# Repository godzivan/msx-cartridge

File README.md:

# MSX Cartridge

Some hardware specs (schematics + PCB designs) to build cartridges for 
MSX system.

## RPMC 
### RPMC is a MSX clone with a real MSX cartridge extension board.
Here is the latest PCB gerber file and schematic.<br/>
[RPMC V2019-1](https://drive.google.com/open?id=1N0of_Qc8jfkX5S-HGIQiXc7S8SLOvJMs) <br/>
[Schematic](https://github.com/meesokim/msx-cartridge/blob/master/rpmcv2019-1/output/rpmcv2019-1.pdf) <br/>
<div style="display:table-cell; vertical-align:middle; text-align:center">
</div><br/>
<br>

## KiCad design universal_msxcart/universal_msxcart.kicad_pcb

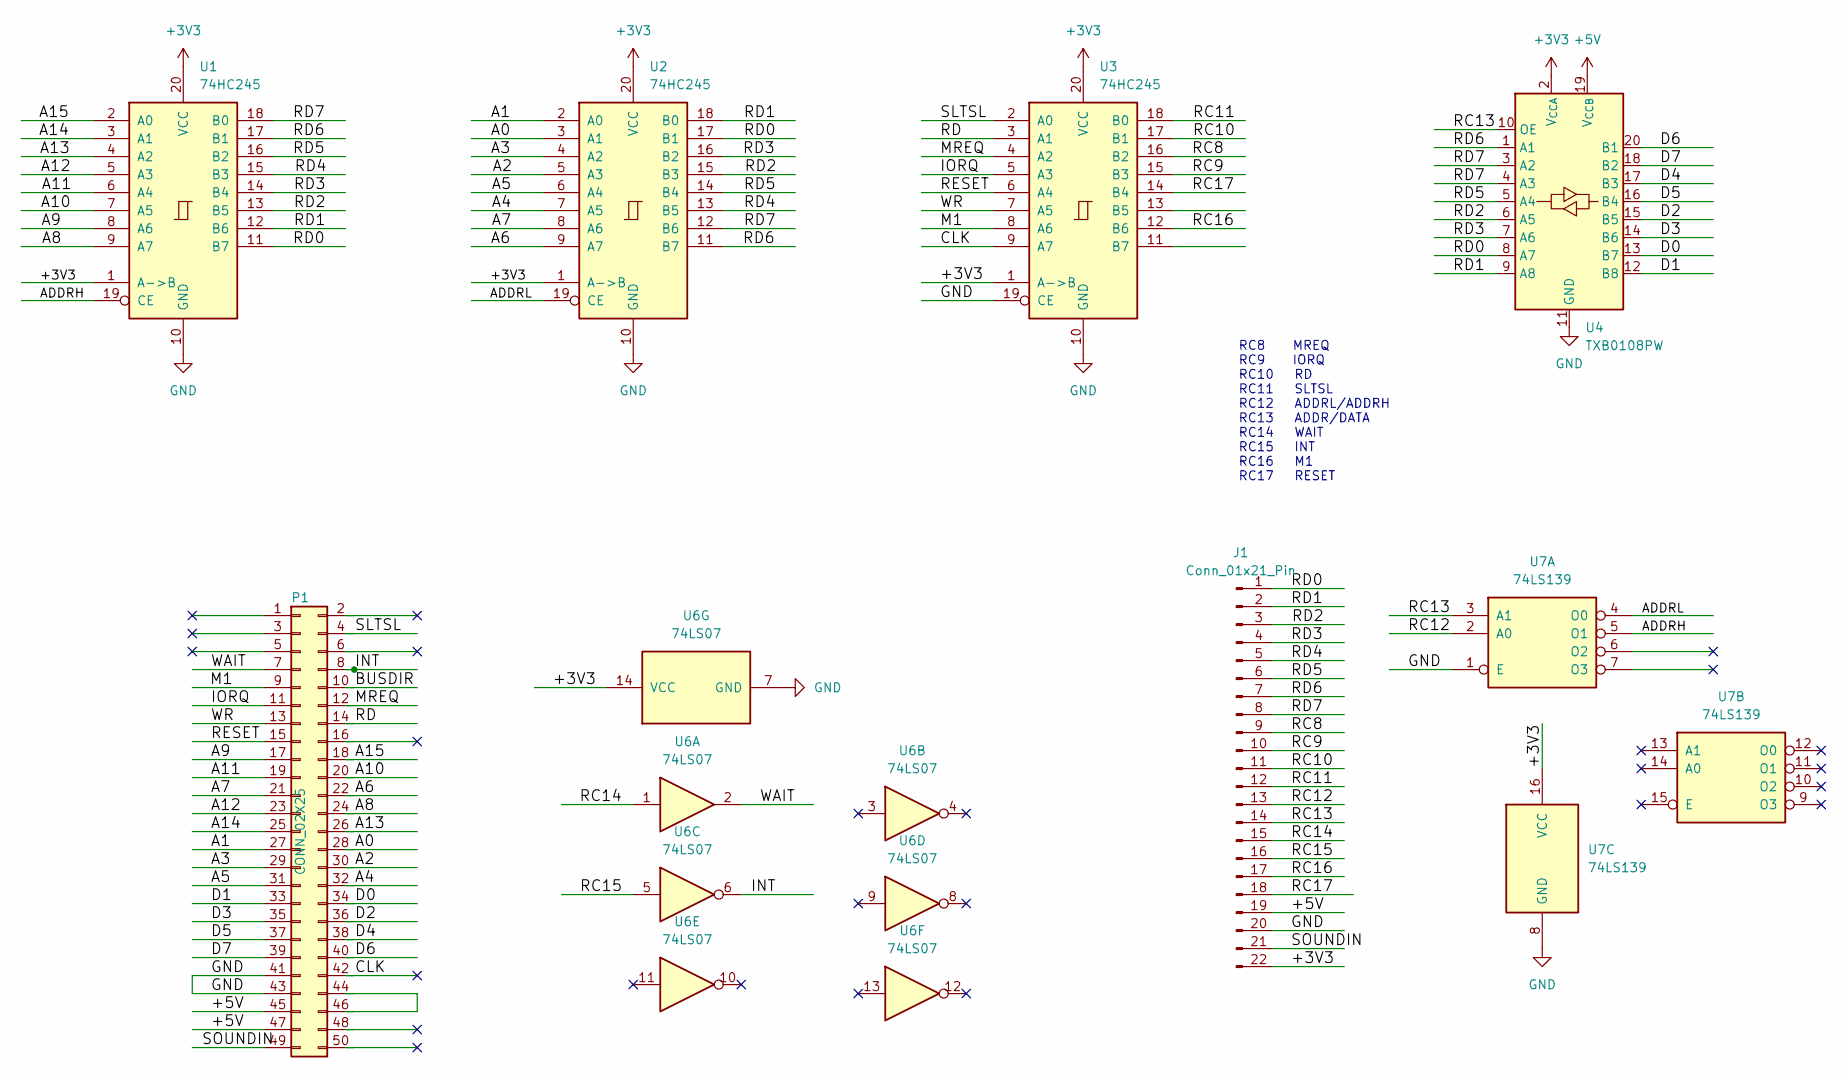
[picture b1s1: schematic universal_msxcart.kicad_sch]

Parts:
J1: Conn_01x21_Pin; PinSocket_1x22_P2.54mm_Horizontal
P1: CONN_02X25; msx_cartridge
U1, U2, U3: 74HC245; SOP-20_7.5x12.8mm_P1.27mm
U4: TXB0108PW; TSSOP-20_L6.5-W4.4-P0.65-LS6.4-BL
U6: 74LS07; SOIC-14_3.9x8.7mm_P1.27mm
U7: 74LS139

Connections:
+3V3: J1.22, U1.1 (A->B), U1.20 (VCC), U2.1 (A->B), U2.20 (VCC), U3.1 (A->B), U3.20 (VCC), U4.2 (V_{CCA}), U6.14 (VCC), U7.16 (VCC)
+5V: J1.19, P1.45, P1.47, U4.19 (V_{CCB})
/A0: P1.28, U2.3 (A1)
/A1: P1.27, U2.2 (A0)
/A2: P1.30, U2.5 (A3)
/A3: P1.29, U2.4 (A2)
/A4: P1.32, U2.7 (A5)
/A5: P1.31, U2.6 (A4)
/A6: P1.22, U2.9 (A7)
/A7: P1.21, U2.8 (A6)
/A8: P1.24, U1.9 (A7)
/A9: P1.17, U1.8 (A6)
/A10: P1.20, U1.7 (A5)
/A11: P1.19, U1.6 (A4)
/A12: P1.23, U1.5 (A3)
/A13: P1.26, U1.4 (A2)
/A14: P1.25, U1.3 (A1)
/A15: P1.18, U1.2 (A0)
/ADDRH: U1.19 (CE), U7.5 (O1)
/ADDRL: U2.19 (CE), U7.4 (O0)
/BUSDIR: P1.10
/CLK: P1.42, U3.9 (A7)
/D0: P1.34, U4.13 (B7)
/D1: P1.33, U4.12 (B8)
/D2: P1.36, U4.15 (B5)
/D3: P1.35, U4.14 (B6)
/D4: P1.38, U4.17 (B3)
/D5: P1.37, U4.16 (B4)
/D6: P1.40, U4.20 (B1)
/D7: P1.39, U4.18 (B2)
/INT: P1.8, U6.6
/IORQ: P1.11, U3.5 (A3)
/M1: P1.9, U3.8 (A6)
/MREQ: P1.12, U3.4 (A2)
/RC8: J1.9, U3.16 (B2)
/RC9: J1.10, U3.15 (B3)
/RC10: J1.11, U3.17 (B1)
/RC11: J1.12, U3.18 (B0)
/RC12: J1.13, U7.2 (A0)
/RC13: J1.14, U4.10 (OE), U7.3 (A1)
/RC14: J1.15, U6.1
/RC15: J1.16, U6.5
/RC16: J1.17, U3.12 (B6)
/RC17: J1.18, U3.14 (B4)
/RD: P1.14, U3.3 (A1)
/RD0: J1.1, U1.11 (B7), U2.17 (B1), U4.8 (A7)
/RD1: J1.2, U1.12 (B6), U2.18 (B0), U4.9 (A8)
/RD2: J1.3, U1.13 (B5), U2.15 (B3), U4.6 (A5)
/RD3: J1.4, U1.14 (B4), U2.16 (B2), U4.7 (A6)
/RD4: J1.5, U1.15 (B3), U2.13 (B5)
/RD5: J1.6, U1.16 (B2), U2.14 (B4), U4.5 (A4)
/RD6: J1.7, U1.17 (B1), U2.11 (B7), U4.1 (A1)
/RD7: J1.8, U1.18 (B0), U2.12 (B6), U4.3 (A2), U4.4 (A3)
/RESET: P1.15, U3.6 (A4)
/SLTSL: P1.4, U3.2 (A0)
/SOUNDIN: J1.21, P1.49
/WAIT: P1.7, U6.2
/WR: P1.13, U3.7 (A5)
GND: J1.20, P1.41, P1.43, U1.10 (GND), U2.10 (GND), U3.10 (GND), U3.19 (CE), U4.11 (GND), U6.7 (GND), U7.1 (E), U7.8 (GND)

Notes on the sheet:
RC8 MREQ RC9 IORQ RC10 RD RC11 SLTSL RC12 ADDRL/ADDRH RC13 ADDR/DATA RC14 WAIT RC15 INT RC16 M1 RC17 RESET

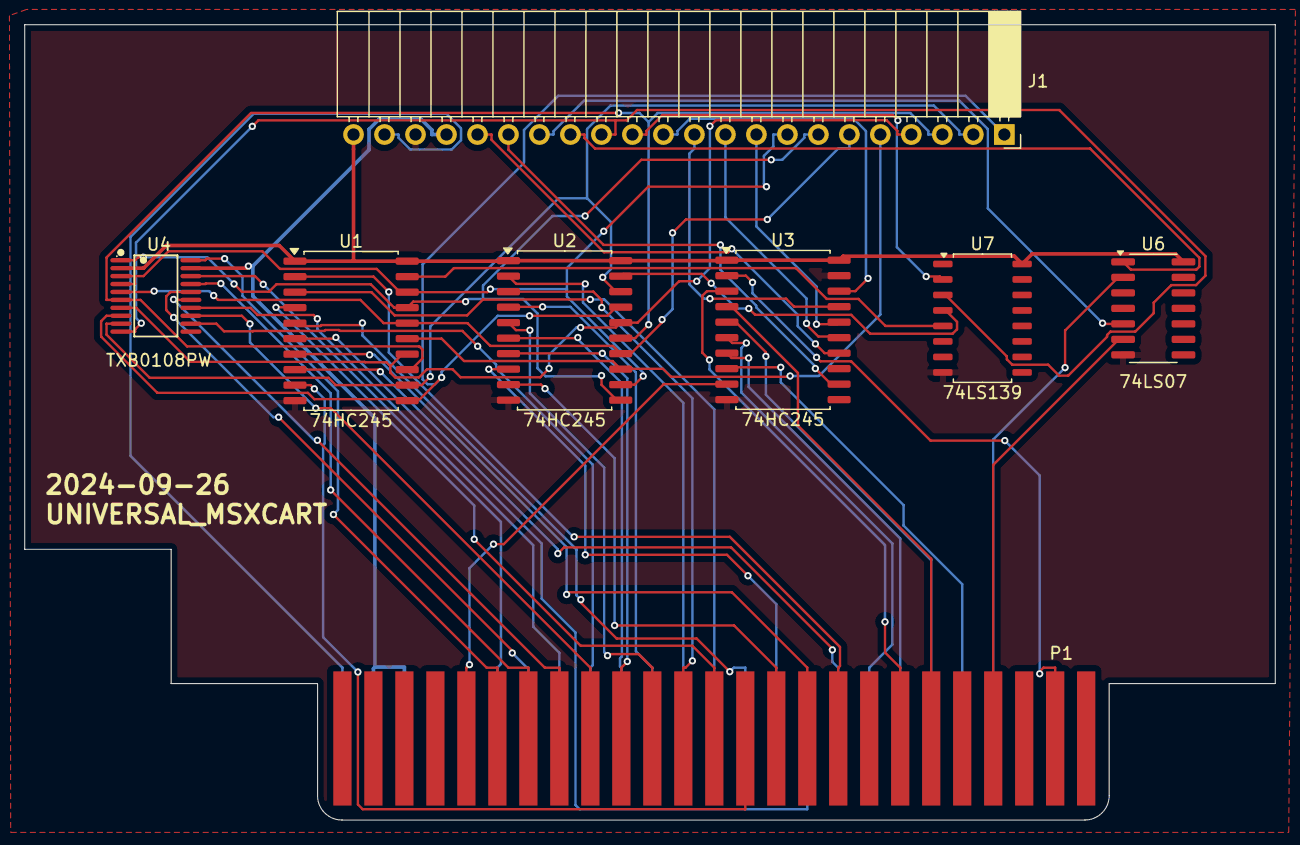
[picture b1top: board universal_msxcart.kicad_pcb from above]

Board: 2 copper layers, 102.5 x 65.2 mm, 8 parts (0 on the bottom side), 58 nets.

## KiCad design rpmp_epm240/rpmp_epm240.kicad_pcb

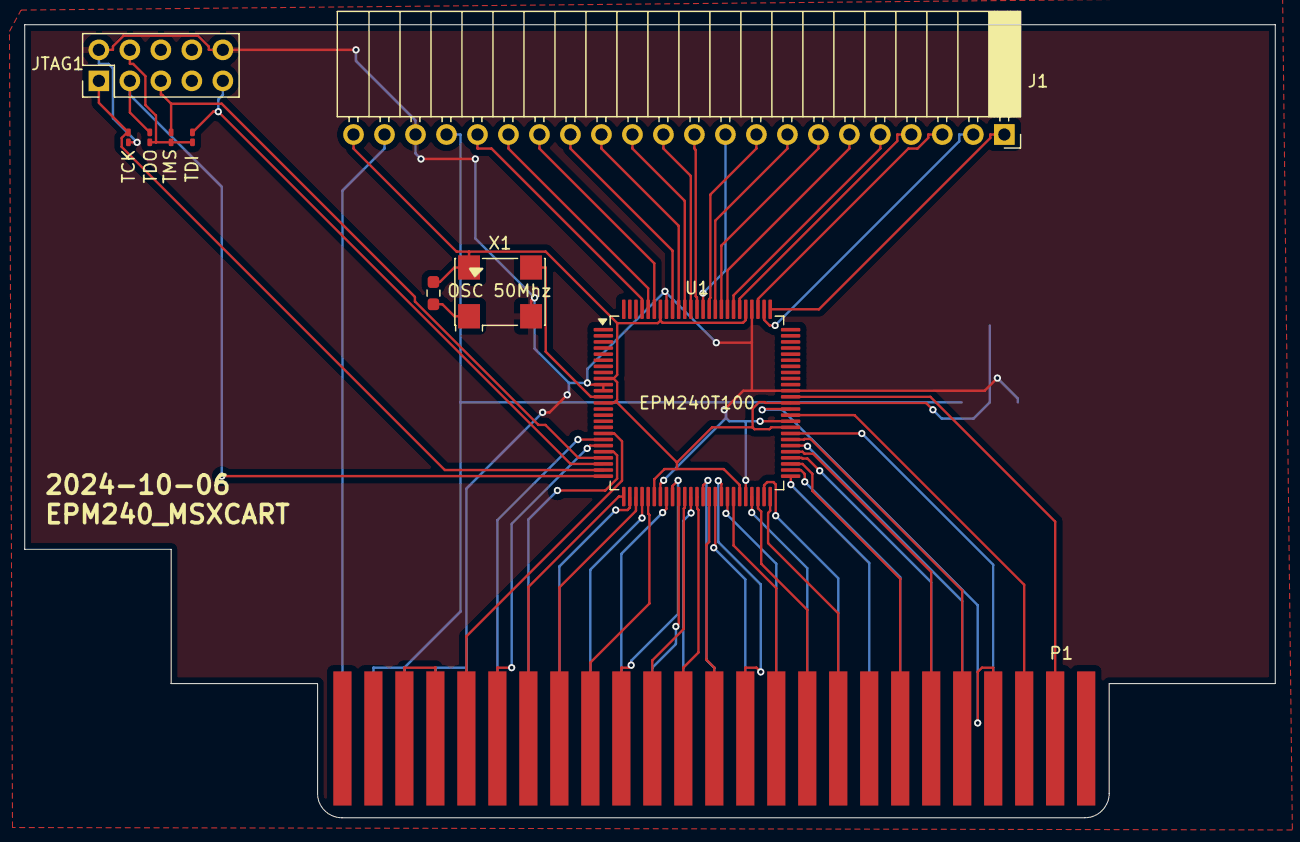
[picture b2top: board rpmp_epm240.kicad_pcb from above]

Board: 2 copper layers, 102.5 x 65.0 mm, 11 parts (1 on the bottom side), 66 nets.

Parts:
J1: Conn_01x21_Pin; PinSocket_1x22_P2.54mm_Horizontal
JTAG1: CONN_02X05; PinHeader_2x05_P2.54mm_Vertical
P1: CONN_02X25; msx_cartridge
R5: R; R_0603_1608Metric_Pad0.98x0.95mm_HandSolder
TCK: 10K; R_0201_0603Metric_Pad0.64x0.40mm_HandSolder
TDI: 10K; R_0201_0603Metric_Pad0.64x0.40mm_HandSolder
TDO: 10K; R_0201_0603Metric_Pad0.64x0.40mm_HandSolder
TMS: 10K; R_0201_0603Metric_Pad0.64x0.40mm_HandSolder
U1: EPM240T100; LQFP-100_14x14mm_P0.5mm
U2: AMS1117-3.3; SOT-223-3_TabPin2
X1: OSC 50Mhz; Oscillator_SMD_Abracon_ASV-4Pin_7.0x5.1mm

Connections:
+3V3: J1.22, R5.1, U1.9 (VCCIO1), U1.13 (VCCINT), U1.31 (VCCIO1), U1.45 (VCCIO1), U1.59 (VCCIO2), U1.63 (VCCINT), U1.80 (VCCIO2), U1.94 (VCCIO2), U2.2 (VO), X1.4 (Vdd)
/3V3: JTAG1.4, TDI.1, TDO.1, TMS.1
/+5V: J1.19, P1.45, P1.47, U2.3 (VI)
/A0: P1.28, U1.38 (IO1_38)
/A1: P1.27, U1.37 (IO1_37)
/A2: P1.30, U1.36 (IO1_36)
/A3: P1.29, U1.35 (IO1_35)
/A4: P1.32, U1.34 (IO1_34)
/A5: P1.31, U1.33 (IO1_33)
/A6: P1.22, U1.44 (IO1_44/DEV_CLRn)
/A7: P1.21, U1.43 (IO1_43/DEV_OE)
/A8: P1.24, U1.42 (IO1_42)
/A9: P1.17, U1.49 (IO1_49)
/A10: P1.20, U1.48 (IO1_48)
/A11: P1.19, U1.47 (IO1_47)
/A12: P1.23, U1.41 (IO1_41)
/A13: P1.26, U1.40 (IO1_40)
/A14: P1.25, U1.39 (IO1_39)
/A15: P1.18, U1.50 (IO1_50)
/BUSDIR: P1.10, U1.57 (IO2_57)
/CLOCK: P1.42, U1.18 (IO1_18)
/D0: P1.34, U1.30 (IO1_30)
/D1: P1.33, U1.29 (IO1_29)
/D2: P1.36, U1.28 (IO1_28)
/D3: P1.35, U1.27 (IO1_27)
/D4: P1.38, U1.26 (IO1_26)
/D5: P1.37, U1.21 (IO1_21)
/D6: P1.40, U1.20 (IO1_20)
/D7: P1.39, U1.19 (IO1_19)
/GCLK: U1.12 (IO1_12/GCLK0), X1.3 (OUT)
/INT: P1.8, U1.62 (IO2_62/GCLK2)
/IORQ: P1.11, U1.54 (IO2_54)
/M1: P1.9, U1.56 (IO2_56)
/MREQ: P1.12, U1.55 (IO2_55)
/RC8: J1.9, U1.86 (IO2_86)
/RC9: J1.10, U1.87 (IO2_87)
/RC10: J1.11, U1.88 (IO2_88)
/RC11: J1.12, U1.89 (IO2_89)
/RC12: J1.13, U1.90 (IO2_90)
/RC13: J1.14, U1.91 (IO2_91)
/RC14: J1.15, U1.92 (IO2_92)
/RC15: J1.16, U1.95 (IO2_95)
/RC16: J1.17, U1.96 (IO2_96)
/RC17: J1.18, U1.97 (IO2_97)
/RD: P1.14, U1.53 (IO2_53)
/RD0: J1.1, U1.76 (IO2_76)
/RD1: J1.2, U1.77 (IO2_77)
/RD2: J1.3, U1.78 (IO2_78)
/RD3: J1.4, U1.81 (IO2_81)
/RD4: J1.5, U1.82 (IO2_82)
/RD5: J1.6, U1.83 (IO2_83)
/RD6: J1.7, U1.84 (IO2_84)
/RD7: J1.8, U1.85 (IO2_85)
/RESET: P1.15, U1.51 (IO1_51)
/RFSH: P1.6, U1.61 (IO2_61)
/SLTSL: P1.4, U1.64 (IO2_64/GCLK3)
/SOUNDIN: J1.21, P1.49
/TCK: JTAG1.1, TCK.2, U1.24 (TCK)
/TDI: JTAG1.9, TDI.2, U1.23 (TDI)
/TDO: JTAG1.3, TDO.2, U1.25 (TDO)
/TMS: JTAG1.5, TMS.2, U1.22 (TMS)
/WAIT: P1.7, U1.58 (IO2_58)
/WR: P1.13, U1.52 (IO2_52)
GND: J1.20, JTAG1.2, JTAG1.10, P1.41, P1.43, TCK.1, U1.10 (GNDIO), U1.11 (GNDINT), U1.32 (GNDIO), U1.46 (GNDIO), U1.60 (GNDIO), U1.65 (GNDINT), U1.79 (GNDIO), U1.93 (GNDIO), U2.1 (GND), X1.2 (GND)
unnamed: P1.44, P1.46
unnamed: R5.2, X1.1 (EN)

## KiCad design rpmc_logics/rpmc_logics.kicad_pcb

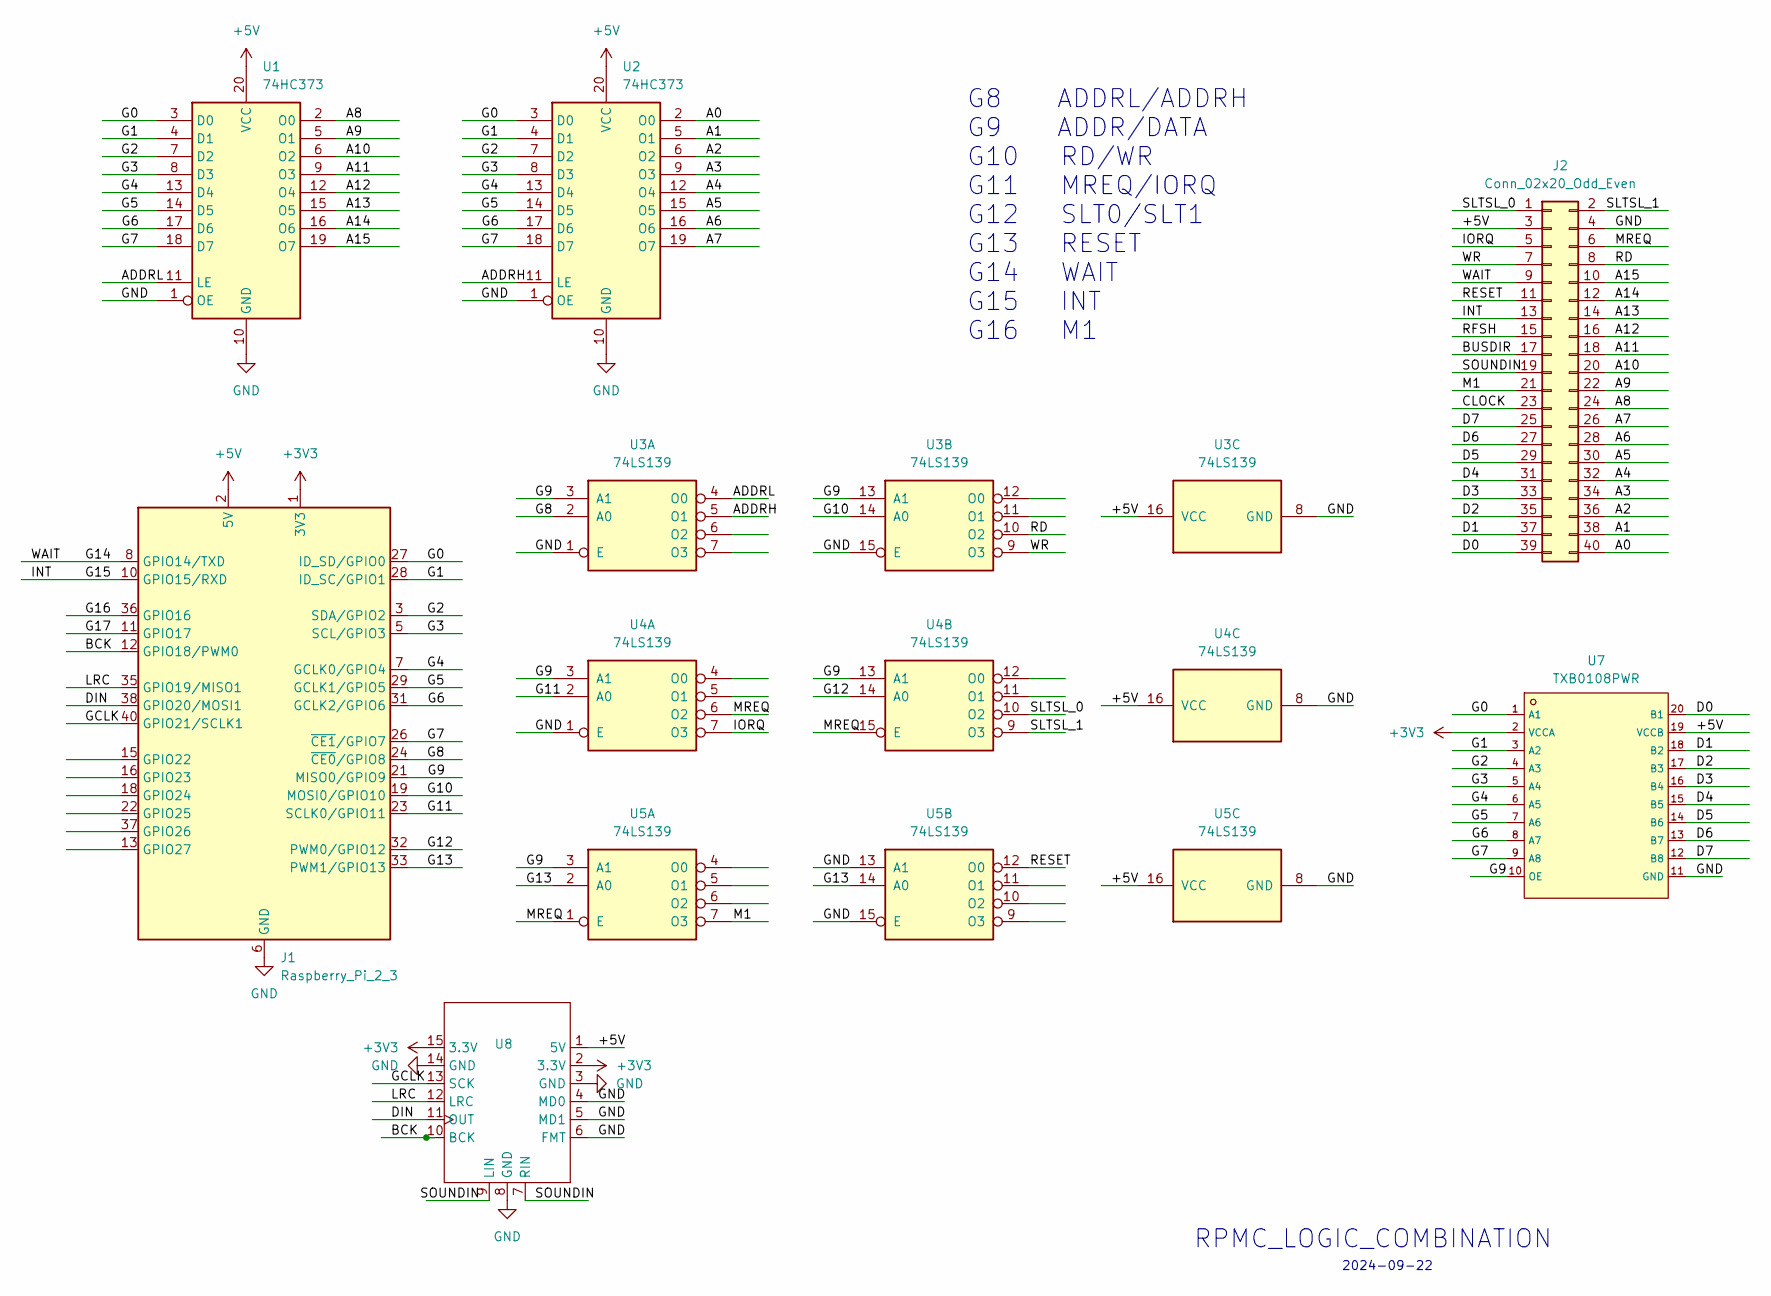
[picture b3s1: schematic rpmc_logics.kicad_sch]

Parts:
J1: Raspberry_Pi_2_3; PinHeader_2x20_P2.54mm_Vertical
J2: Conn_02x20_Odd_Even; PinHeader_2x20_P2.54mm_Vertical
U1, U2: 74HC373; SOIC-20_L13.0-W7.6-P1.27-LS10.3-BL
U3, U4, U5: 74LS139; SOIC-16W_5.3x10.2mm_P1.27mm
U7: TXB0108PWR; TSSOP-20_L6.5-W4.4-P0.65-LS6.4-BL; LCSC C53406
U8: PCM1808_EVB

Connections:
+3V3: J1.1 (3V3), J1.17 (3V3), U7.2 (VCCA), U8.2 (3.3V), U8.15 (3.3V)
+5V: J1.2 (5V), J1.4 (5V), J2.3, U1.20 (VCC), U2.20 (VCC), U3.16 (VCC), U4.16 (VCC), U5.16 (VCC), U7.19 (VCCB), U8.1 (5V)
/A0: J2.40, U2.2 (O0)
/A1: J2.38, U2.5 (O1)
/A2: J2.36, U2.6 (O2)
/A3: J2.34, U2.9 (O3)
/A4: J2.32, U2.12 (O4)
/A5: J2.30, U2.15 (O5)
/A6: J2.28, U2.16 (O6)
/A7: J2.26, U2.19 (O7)
/A8: J2.24, U1.2 (O0)
/A9: J2.22, U1.5 (O1)
/A10: J2.20, U1.6 (O2)
/A11: J2.18, U1.9 (O3)
/A12: J2.16, U1.12 (O4)
/A13: J2.14, U1.15 (O5)
/A14: J2.12, U1.16 (O6)
/A15: J2.10, U1.19 (O7)
/ADDRH: U2.11 (LE), U3.5 (O1)
/ADDRL: U1.11 (LE), U3.4 (O0)
/BCK: J1.12 (GPIO18/PWM0), U8.10 (BCK)
/BUSDIR: J2.17
/CLOCK: J2.23
/D0: J2.39, U7.20 (B1)
/D1: J2.37, U7.18 (B2)
/D2: J2.35, U7.17 (B3)
/D3: J2.33, U7.16 (B4)
/D4: J2.31, U7.15 (B5)
/D5: J2.29, U7.14 (B6)
/D6: J2.27, U7.13 (B7)
/D7: J2.25, U7.12 (B8)
/DIN: J1.38 (GPIO20/MOSI1), U8.11 (OUT)
/G0: J1.27 (ID_SD/GPIO0), U1.3 (D0), U2.3 (D0), U7.1 (A1)
/G1: J1.28 (ID_SC/GPIO1), U1.4 (D1), U2.4 (D1), U7.3 (A2)
/G2: J1.3 (SDA/GPIO2), U1.7 (D2), U2.7 (D2), U7.4 (A3)
/G3: J1.5 (SCL/GPIO3), U1.8 (D3), U2.8 (D3), U7.5 (A4)
/G4: J1.7 (GCLK0/GPIO4), U1.13 (D4), U2.13 (D4), U7.6 (A5)
/G5: J1.29 (GCLK1/GPIO5), U1.14 (D5), U2.14 (D5), U7.7 (A6)
/G6: J1.31 (GCLK2/GPIO6), U1.17 (D6), U2.17 (D6), U7.8 (A7)
/G7: J1.26 (~CE1/GPIO7), U1.18 (D7), U2.18 (D7), U7.9 (A8)
/G8: J1.24 (~CE0/GPIO8), U3.2 (A0)
/G9: J1.21 (MISO0/GPIO9), U3.3 (A1), U3.13 (A1), U4.3 (A1), U4.13 (A1), U5.3 (A1), U7.10 (OE)
/G10: J1.19 (MOSI0/GPIO10), U3.14 (A0)
/G11: J1.23 (SCLK0/GPIO11), U4.2 (A0)
/G12: J1.32 (PWM0/GPIO12), U4.14 (A0)
/G13: J1.33 (PWM1/GPIO13), U5.2 (A0), U5.14 (A0)
/G14: J1.8 (GPIO14/TXD), J2.9
/G15: J1.10 (GPIO15/RXD), J2.13
/G16: J1.36 (GPIO16)
/G17: J1.11 (GPIO17)
/GCLK: J1.40 (GPIO21/SCLK1), U8.13 (SCK)
/IORQ: J2.5, U4.7 (O3)
/LRC: J1.35 (GPIO19/MISO1), U8.12 (LRC)
/M1: J2.21, U5.7 (O3)
/MREQ: J2.6, U4.6 (O2), U4.15 (E), U5.1 (E)
/RD: J2.8, U3.10 (O2)
/RESET: J2.11, U5.12 (O0)
/RFSH: J2.15
/SLTSL_0: J2.1, U4.10 (O2)
/SLTSL_1: J2.2, U4.9 (O3)
/SOUNDIN: J2.19, U8.7 (RIN), U8.9 (LIN)
/WR: J2.7, U3.9 (O3)
GND: J1.6 (GND), J1.9 (GND), J1.14 (GND), J1.20 (GND), J1.25 (GND), J1.30 (GND), J1.34 (GND), J1.39 (GND), J2.4, U1.1 (OE), U1.10 (GND), U2.1 (OE), U2.10 (GND), U3.1 (E), U3.8 (GND), U3.15 (E), U4.1 (E), U4.8 (GND), U5.8 (GND), U5.13 (A1), U5.15 (E), U7.11 (GND), U8.3 (GND), U8.4 (MD0), U8.5 (MD1), U8.6 (FMT), U8.8 (GND), U8.14 (GND)

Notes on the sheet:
RPMC_LOGIC_COMBINATION
2024-09-22
G8 ADDRL/ADDRH G9 ADDR/DATA G10 RD/WR G11 MREQ/IORQ G12 SLT0/SLT1 G13 RESET G14 WAIT G15 INT G16 M1

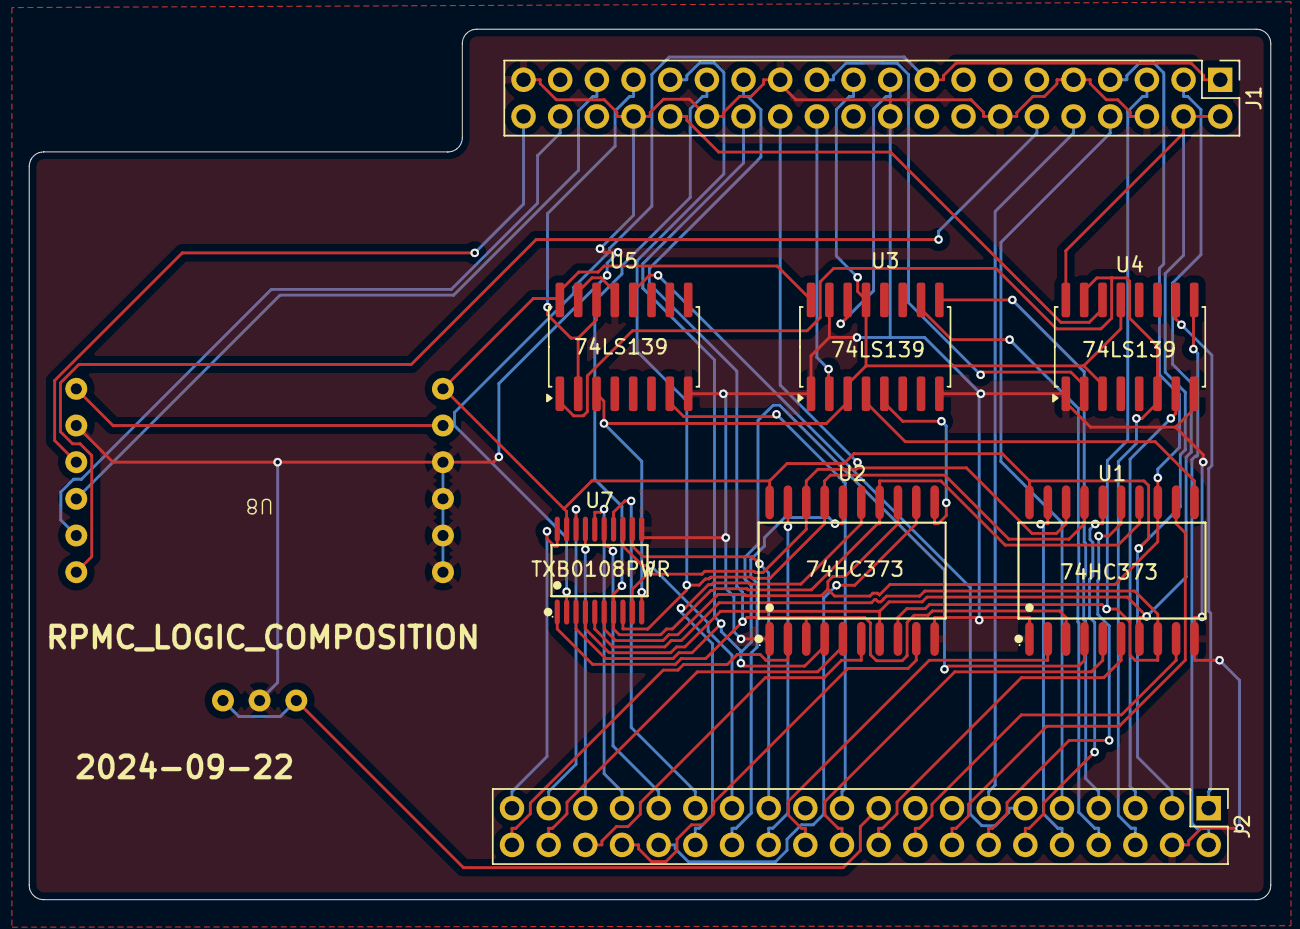
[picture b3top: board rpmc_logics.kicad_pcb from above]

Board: 2 copper layers, 86.0 x 60.3 mm, 9 parts (0 on the bottom side), 58 nets.

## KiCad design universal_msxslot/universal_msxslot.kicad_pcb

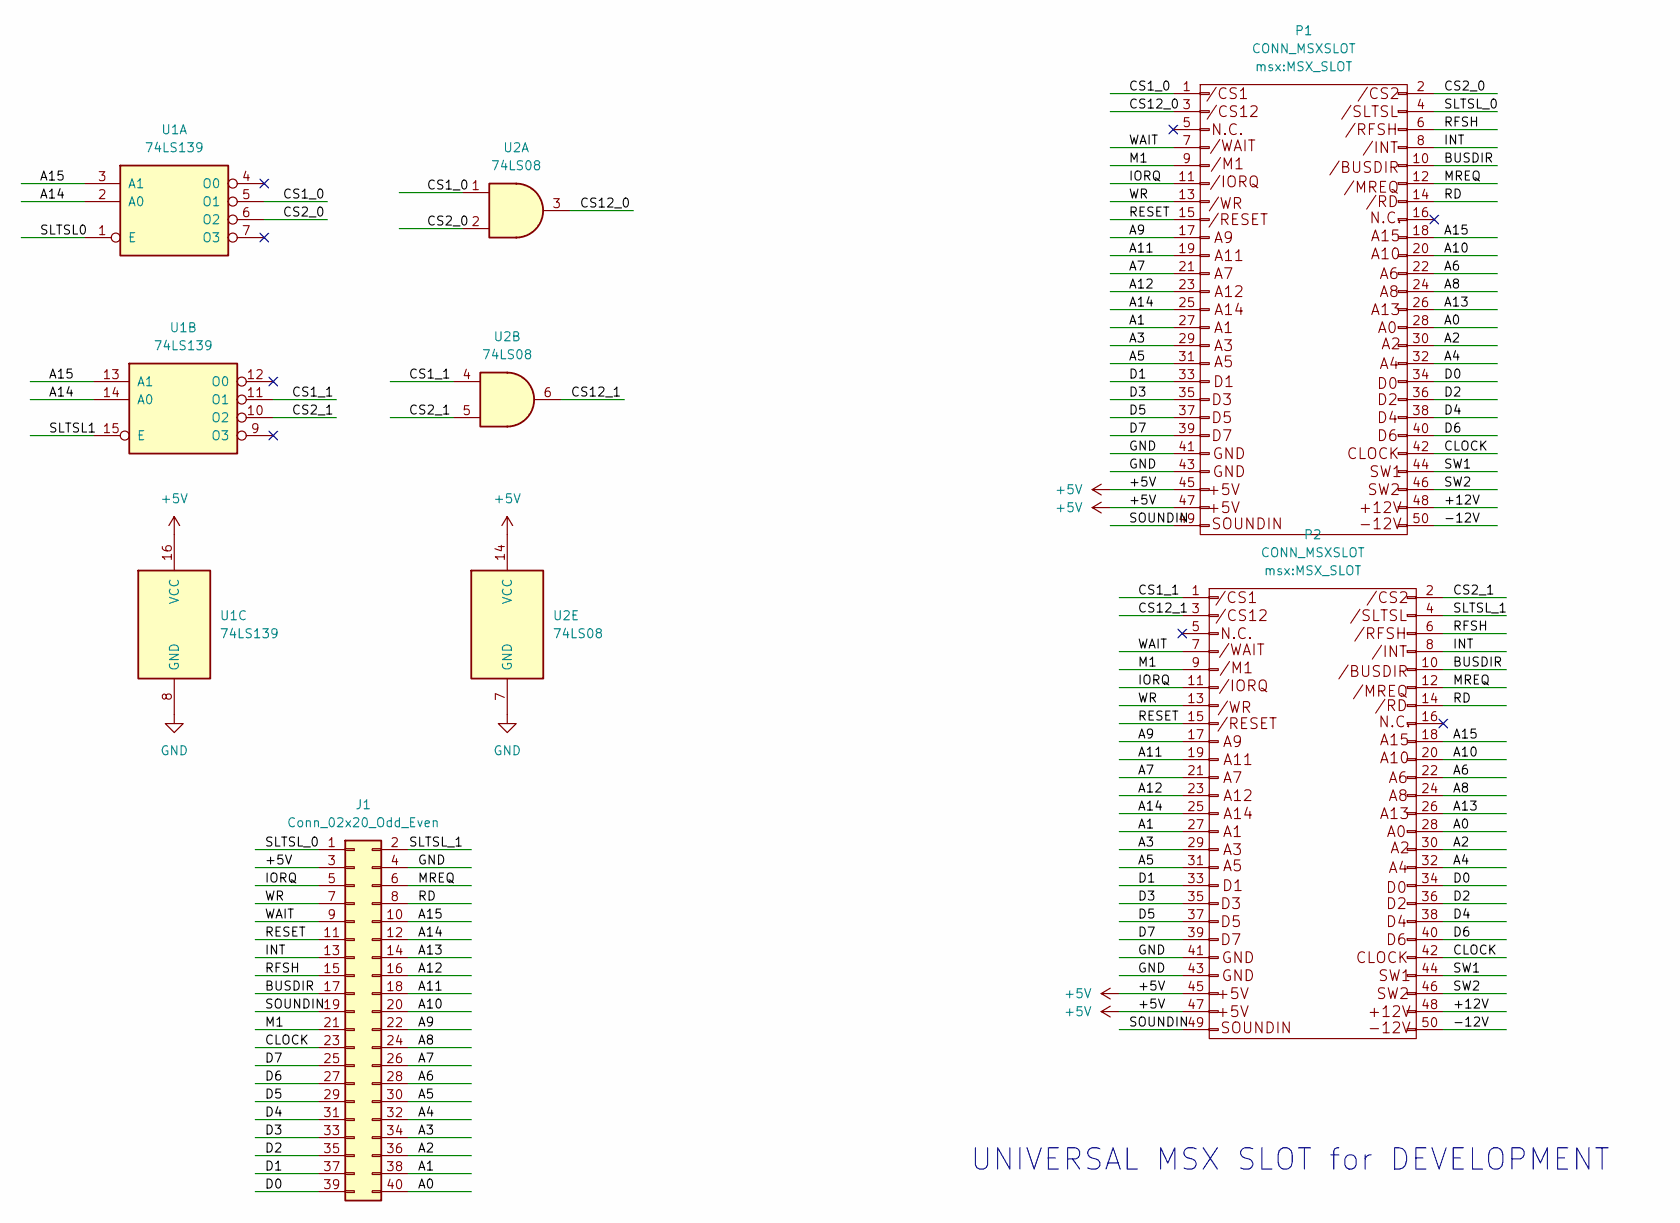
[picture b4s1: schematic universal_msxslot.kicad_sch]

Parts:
J1: Conn_02x20_Odd_Even; PinSocket_2x20_P2.54mm_Vertical_SMD_DIP
P1, P2: CONN_MSXSLOT; MSX_SLOT
U1: 74LS139; TSSOP-16_L5.0-W4.4-P0.65-LS6.4-BL
U2: 74LS08; TSSOP-14_L5.0-W4.4-P0.65-LS6.4-BL

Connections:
+5V: J1.3, P1.45, P1.47, P2.45, P2.47, U1.16 (VCC), U2.14 (VCC)
/+12V: P1.48, P2.48
/-12V: P1.50, P2.50
/A0: J1.40, P1.28, P2.28
/A1: J1.38, P1.27, P2.27
/A2: J1.36, P1.30, P2.30
/A3: J1.34, P1.29, P2.29
/A4: J1.32, P1.32, P2.32
/A5: J1.30, P1.31, P2.31
/A6: J1.28, P1.22, P2.22
/A7: J1.26, P1.21, P2.21
/A8: J1.24, P1.24, P2.24
/A9: J1.22, P1.17, P2.17
/A10: J1.20, P1.20, P2.20
/A11: J1.18, P1.19, P2.19
/A12: J1.16, P1.23, P2.23
/A13: J1.14, P1.26, P2.26
/A14: J1.12, P1.25, P2.25, U1.2 (A0), U1.14 (A0)
/A15: J1.10, P1.18, P2.18, U1.3 (A1), U1.13 (A1)
/BUSDIR: J1.17, P1.10, P2.10
/CLOCK: J1.23, P1.42, P2.42
/CS1_0: P1.1, U1.5 (O1), U2.1
/CS1_1: P2.1, U1.11 (O1), U2.4
/CS2_0: P1.2, U1.6 (O2), U2.2
/CS2_1: P2.2, U1.10 (O2), U2.5
/CS12_0: P1.3, U2.3
/CS12_1: P2.3, U2.6
/D0: J1.39, P1.34, P2.34
/D1: J1.37, P1.33, P2.33
/D2: J1.35, P1.36, P2.36
/D3: J1.33, P1.35, P2.35
/D4: J1.31, P1.38, P2.38
/D5: J1.29, P1.37, P2.37
/D6: J1.27, P1.40, P2.40
/D7: J1.25, P1.39, P2.39
/INT: J1.13, P1.8, P2.8
/IORQ: J1.5, P1.11, P2.11
/M1: J1.21, P1.9, P2.9
/MREQ: J1.6, P1.12, P2.12
/RD: J1.8, P1.14, P2.14
/RESET: J1.11, P1.15, P2.15
/RFSH: J1.15, P1.6, P2.6
/SLTSL0: U1.1 (E)
/SLTSL1: U1.15 (E)
/SLTSL_0: J1.1, P1.4
/SLTSL_1: J1.2, P2.4
/SOUNDIN: J1.19, P1.49, P2.49
/SW1: P1.44, P2.44
/SW2: P1.46, P2.46
/WAIT: J1.9, P1.7, P2.7
/WR: J1.7, P1.13, P2.13
GND: J1.4, P1.41, P1.43, P2.41, P2.43, U1.8 (GND), U2.7 (GND)

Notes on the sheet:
UNIVERSAL MSX SLOT for DEVELOPMENT

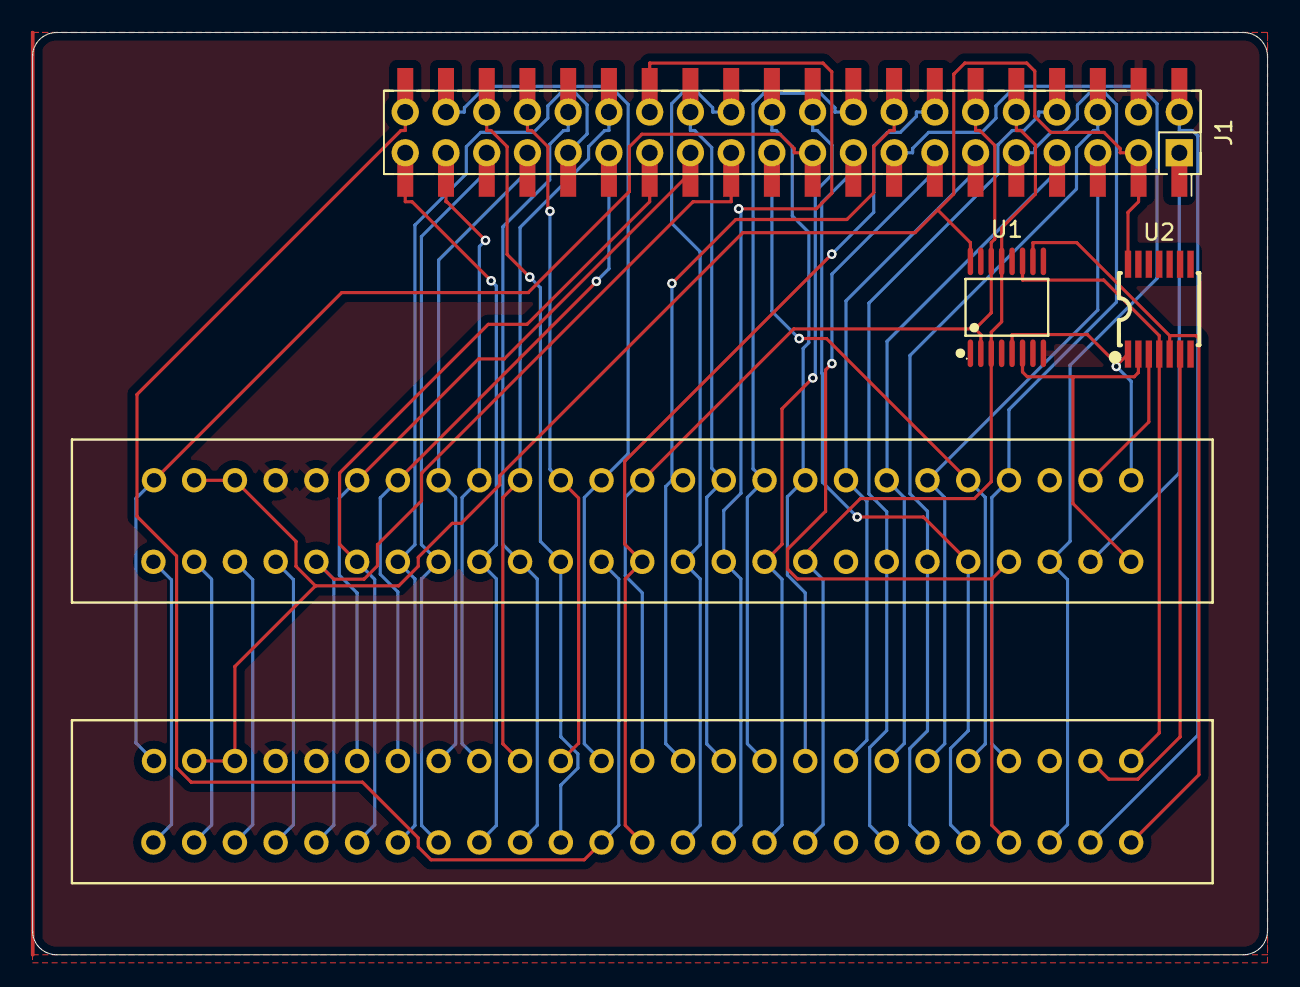
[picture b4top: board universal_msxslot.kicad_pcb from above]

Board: 2 copper layers, 77.0 x 57.5 mm, 5 parts (0 on the bottom side), 50 nets.

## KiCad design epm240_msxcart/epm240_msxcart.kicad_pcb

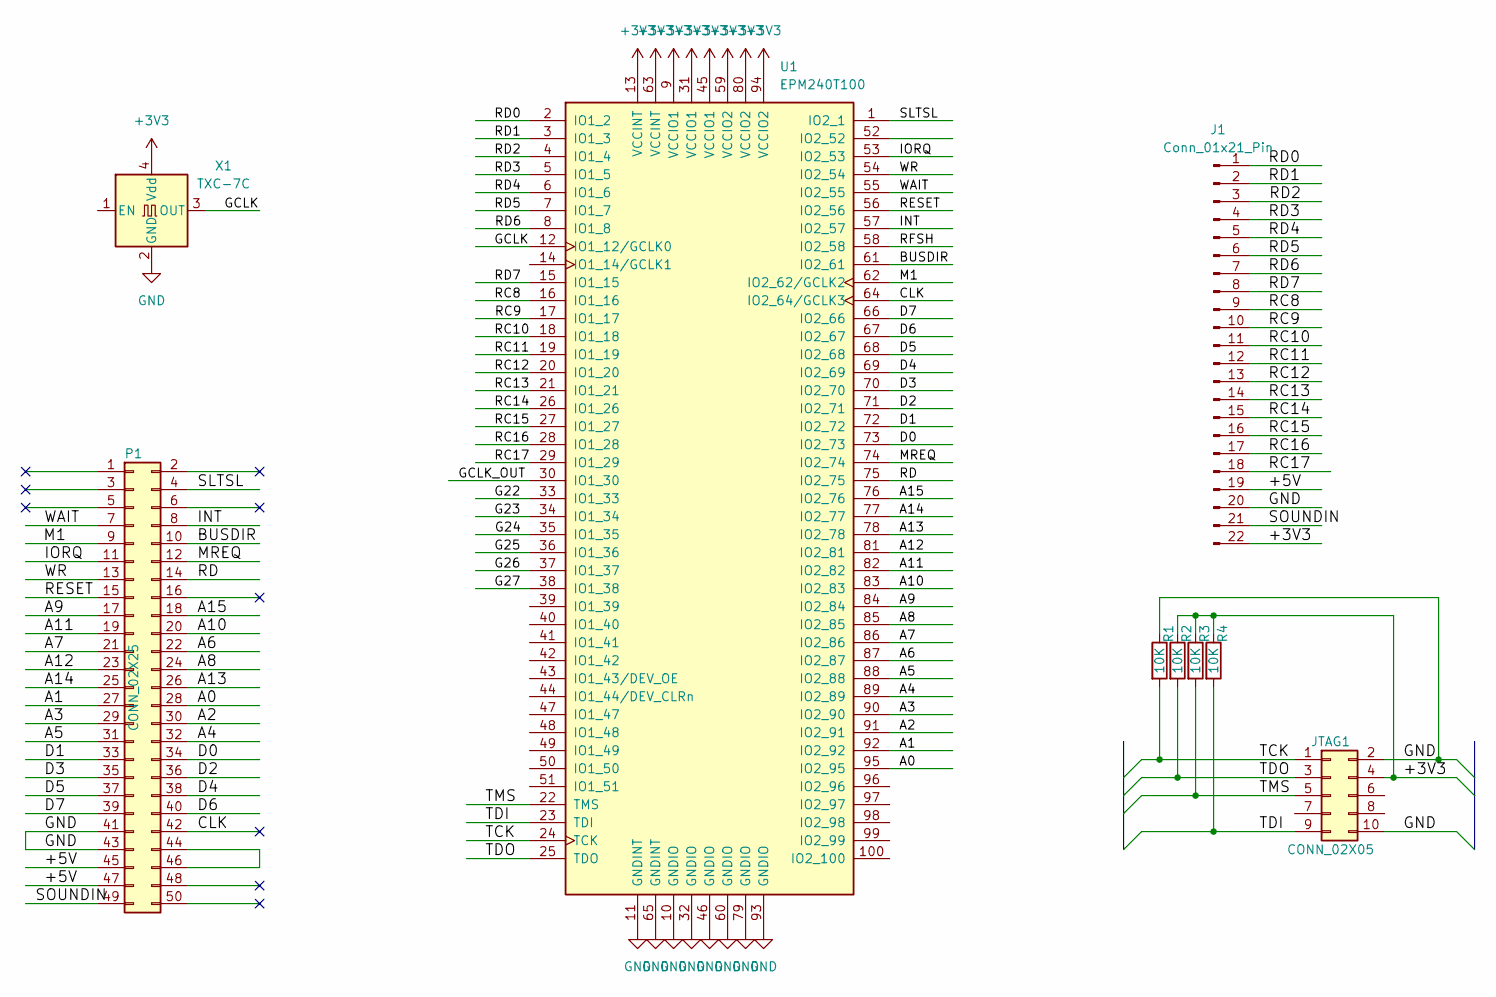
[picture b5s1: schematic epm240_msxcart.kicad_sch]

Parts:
J1: Conn_01x21_Pin; PinSocket_1x22_P2.54mm_Horizontal
JTAG1: CONN_02X05; PinHeader_2x05_P2.54mm_Horizontal
P1: CONN_02X25; card_edge_connector
R1, R2, R3, R4: 10K; R_0201_0603Metric_Pad0.64x0.40mm_HandSolder
U1: EPM240T100; LQFP-100_14x14mm_P0.5mm
X1: TXC-7C; Crystal_SMD_3225-4Pin_3.2x2.5mm_HandSoldering

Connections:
+3V3: J1.22, JTAG1.4, R2.1, R3.1, R4.1, U1.9 (VCCIO1), U1.13 (VCCINT), U1.31 (VCCIO1), U1.45 (VCCIO1), U1.59 (VCCIO2), U1.63 (VCCINT), U1.80 (VCCIO2), U1.94 (VCCIO2), X1.4 (Vdd)
/+5V: J1.19, P1.45, P1.47
/A0: P1.28, U1.95 (IO2_95)
/A1: P1.27, U1.92 (IO2_92)
/A2: P1.30, U1.91 (IO2_91)
/A3: P1.29, U1.90 (IO2_90)
/A4: P1.32, U1.89 (IO2_89)
/A5: P1.31, U1.88 (IO2_88)
/A6: P1.22, U1.87 (IO2_87)
/A7: P1.21, U1.86 (IO2_86)
/A8: P1.24, U1.85 (IO2_85)
/A9: P1.17, U1.84 (IO2_84)
/A10: P1.20, U1.83 (IO2_83)
/A11: P1.19, U1.82 (IO2_82)
/A12: P1.23, U1.81 (IO2_81)
/A13: P1.26, U1.78 (IO2_78)
/A14: P1.25, U1.77 (IO2_77)
/A15: P1.18, U1.76 (IO2_76)
/BUSDIR: P1.10, U1.61 (IO2_61)
/CLK: P1.42, U1.64 (IO2_64/GCLK3)
/D0: P1.34, U1.73 (IO2_73)
/D1: P1.33, U1.72 (IO2_72)
/D2: P1.36, U1.71 (IO2_71)
/D3: P1.35, U1.70 (IO2_70)
/D4: P1.38, U1.69 (IO2_69)
/D5: P1.37, U1.68 (IO2_68)
/D6: P1.40, U1.67 (IO2_67)
/D7: P1.39, U1.66 (IO2_66)
/G22: U1.33 (IO1_33)
/G23: U1.34 (IO1_34)
/G24: U1.35 (IO1_35)
/G25: U1.36 (IO1_36)
/G26: U1.37 (IO1_37)
/G27: U1.38 (IO1_38)
/GCLK: U1.12 (IO1_12/GCLK0), X1.3 (OUT)
/GCLK_OUT: U1.30 (IO1_30)
/INT: P1.8, U1.57 (IO2_57)
/IORQ: P1.11, U1.53 (IO2_53)
/M1: P1.9, U1.62 (IO2_62/GCLK2)
/MREQ: P1.12, U1.74 (IO2_74)
/RC8: J1.9, U1.16 (IO1_16)
/RC9: J1.10, U1.17 (IO1_17)
/RC10: J1.11, U1.18 (IO1_18)
/RC11: J1.12, U1.19 (IO1_19)
/RC12: J1.13, U1.20 (IO1_20)
/RC13: J1.14, U1.21 (IO1_21)
/RC14: J1.15, U1.26 (IO1_26)
/RC15: J1.16, U1.27 (IO1_27)
/RC16: J1.17, U1.28 (IO1_28)
/RC17: J1.18, U1.29 (IO1_29)
/RD: P1.14, U1.75 (IO2_75)
/RD0: J1.1, U1.2 (IO1_2)
/RD1: J1.2, U1.3 (IO1_3)
/RD2: J1.3, U1.4 (IO1_4)
/RD3: J1.4, U1.5 (IO1_5)
/RD4: J1.5, U1.6 (IO1_6)
/RD5: J1.6, U1.7 (IO1_7)
/RD6: J1.7, U1.8 (IO1_8)
/RD7: J1.8, U1.15 (IO1_15)
/RESET: P1.15, U1.56 (IO2_56)
/RFSH: U1.58 (IO2_58)
/SLTSL: P1.4, U1.1 (IO2_1)
/SOUNDIN: J1.21, P1.49
/TCK: JTAG1.1, R1.2, U1.24 (TCK)
/TDI: JTAG1.9, R4.2, U1.23 (TDI)
/TDO: JTAG1.3, R2.2, U1.25 (TDO)
/TMS: JTAG1.5, R3.2, U1.22 (TMS)
/WAIT: P1.7, U1.55 (IO2_55)
/WR: P1.13, U1.54 (IO2_54)
GND: J1.20, JTAG1.2, JTAG1.10, P1.41, P1.43, R1.1, U1.10 (GNDIO), U1.11 (GNDINT), U1.32 (GNDIO), U1.46 (GNDIO), U1.60 (GNDIO), U1.65 (GNDINT), U1.79 (GNDIO), U1.93 (GNDIO), X1.2 (GND)
unnamed: P1.44, P1.46

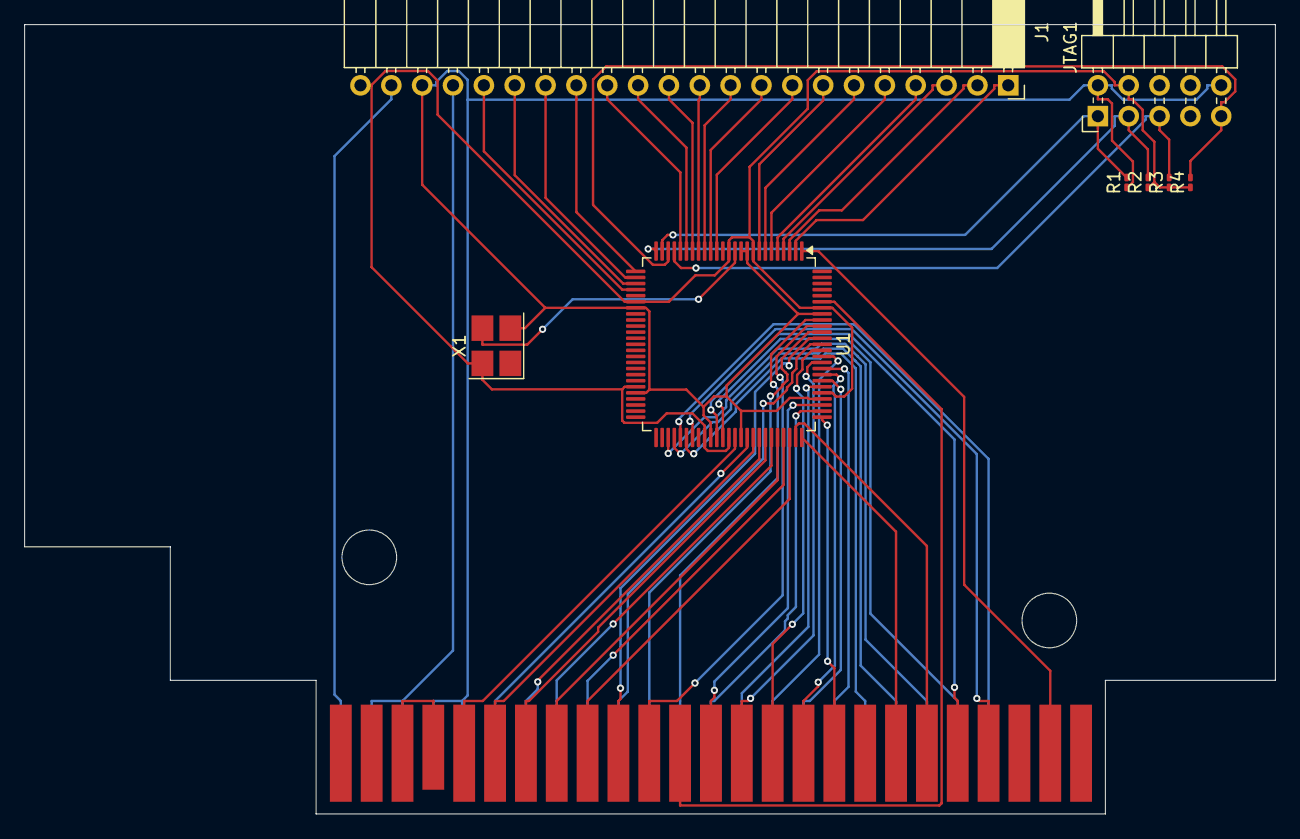
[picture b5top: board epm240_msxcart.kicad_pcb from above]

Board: 2 copper layers, 103.0 x 65.0 mm, 9 parts (0 on the bottom side), 63 nets.
